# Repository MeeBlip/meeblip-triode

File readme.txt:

---------------------------------------------------------------------------------------------------
                     _     _ _         _        _           _      
                    | |   | (_)       | |      (_)         | |     
 _ __ ___   ___  ___| |__ | |_ _ __   | |_ _ __ _  ___   __| | ___ 
| '_ ` _ \ / _ \/ _ \ '_ \| | | '_ \  | __| '__| |/ _ \ / _` |/ _ \
| | | | | |  __/  __/ |_) | | | |_) | | |_| |  | | (_) | (_| |  __/
|_| |_| |_|\___|\___|_.__/|_|_| .__/   \__|_|  |_|\___/ \__,_|\___|
                              | |                                  
                              |_|                                                                                   
---------------------------------------------------------------------------------------------------

Change log

V1.10 2016.11.12 
- Updated MIDI code to exit interrupt immediately if MIDI command is unrecognized
- Increased front panel switch scanning rate (10X faster)
- Reduced pitchbend to ± 3 semitones
- Altered filter decay envelope to ignore SUSTAIN switch so that filter sweeps continue when key is released
- Removed digital pre-filtering code (previously used on OSC A&B)
- Removed digital enveloping of OSC A & B
- Gate oscillators when amplitude envelope hits zero (prevents audio bleed through)
- Changed filter cutoff curve (use table from MeeBlip SE)
- Scale filter cutoff knob to cover 25%-100% of knob range
- Scale filter resonance knob to cover 25%-100% of knob range
- Added bandlimited square wave tables (pulse waves were previously generated with offset sawtooth ramps)
- Raw calculated waveforms are now used in the lower 4 octaves, then switch to bandlimited wavetables. 
-Flipped waveforms to match phase and avoid a pop when crossing the cut-over point
 
V1.01 2016.10.24 
- Ensure MIDI channel settings are saved correctly when powered off for Channel 1-8 (implement MAXMIDI variable)
- Allow MIDI CC control of GLIDE knob to select waves when in wavetable mode (CC 61 now controls GLIDE in wavetable mode)
- Updated MIDI code to exit interrupt immediately if MIDI command is unrecognized
- Increased front panel switch scanning rate (10X faster)

V1.00 2016.10.19 
- Initial release

---------------------------------------------------------------------------------------------------

  MeeBlip hardware is released under a Creative Commons Attribution-ShareAlike 4.0 International 
	(CC-BY-SA 4.0) license. You are free to share and transform this work, even for commercial
	purposes, providing you:

	1. Give appropriate credit, provide a link to the license, and indicate if changes were made. 
	   You can say something such as "This project is based upon the MeeBlip anode synthesizer. 
	   For more information, visit meeblip.com or download source code and design files at 
	   https://github.com/MeeBlip"

	2. If you remix, transform, or build upon the material, you must distribute your contributions
	   under the same license as the original. That means making source code, design files and PC 
	   board layout files available so someone can build and modify their own version of the project. 

	3. The MeeBlip name is our intellectual property. You are not allowed to release commercial 
	   devices based on our designs using the MeeBlip brand name. 
	
	Here's are links to the Creative Commons license, for the design:
	http://creativecommons.org/licenses/by-sa/4.0/
	http://creativecommons.org/licenses/by-sa/4.0/legalcode

	MeeBlip source code and documentation is released under a GPLv3 license. 

  A copy is available in the MeeBlip repository at:
	https://github.com/MeeBlip/meeblip-anode/blob/master/LICENSE

	MeeBlip Contributors

	Jarek Ziembicki	- Created the original AVRsynth, upon which this project is based.
	Laurie Biddulph	- Worked with Jarek to translate his comments into English, ported to Atmega16
	Daniel Kruszyna	- Extended AVRsynth (several of his ideas are incorporated in MeeBlip)
 	Julian Schmidt	- Original Meeblip digital filter algorithm
	Axel Werner		- Code optimization, bug fixes and new bandlimited waveforms 
	James Grahame 	- Meeblip hardware and firmware development

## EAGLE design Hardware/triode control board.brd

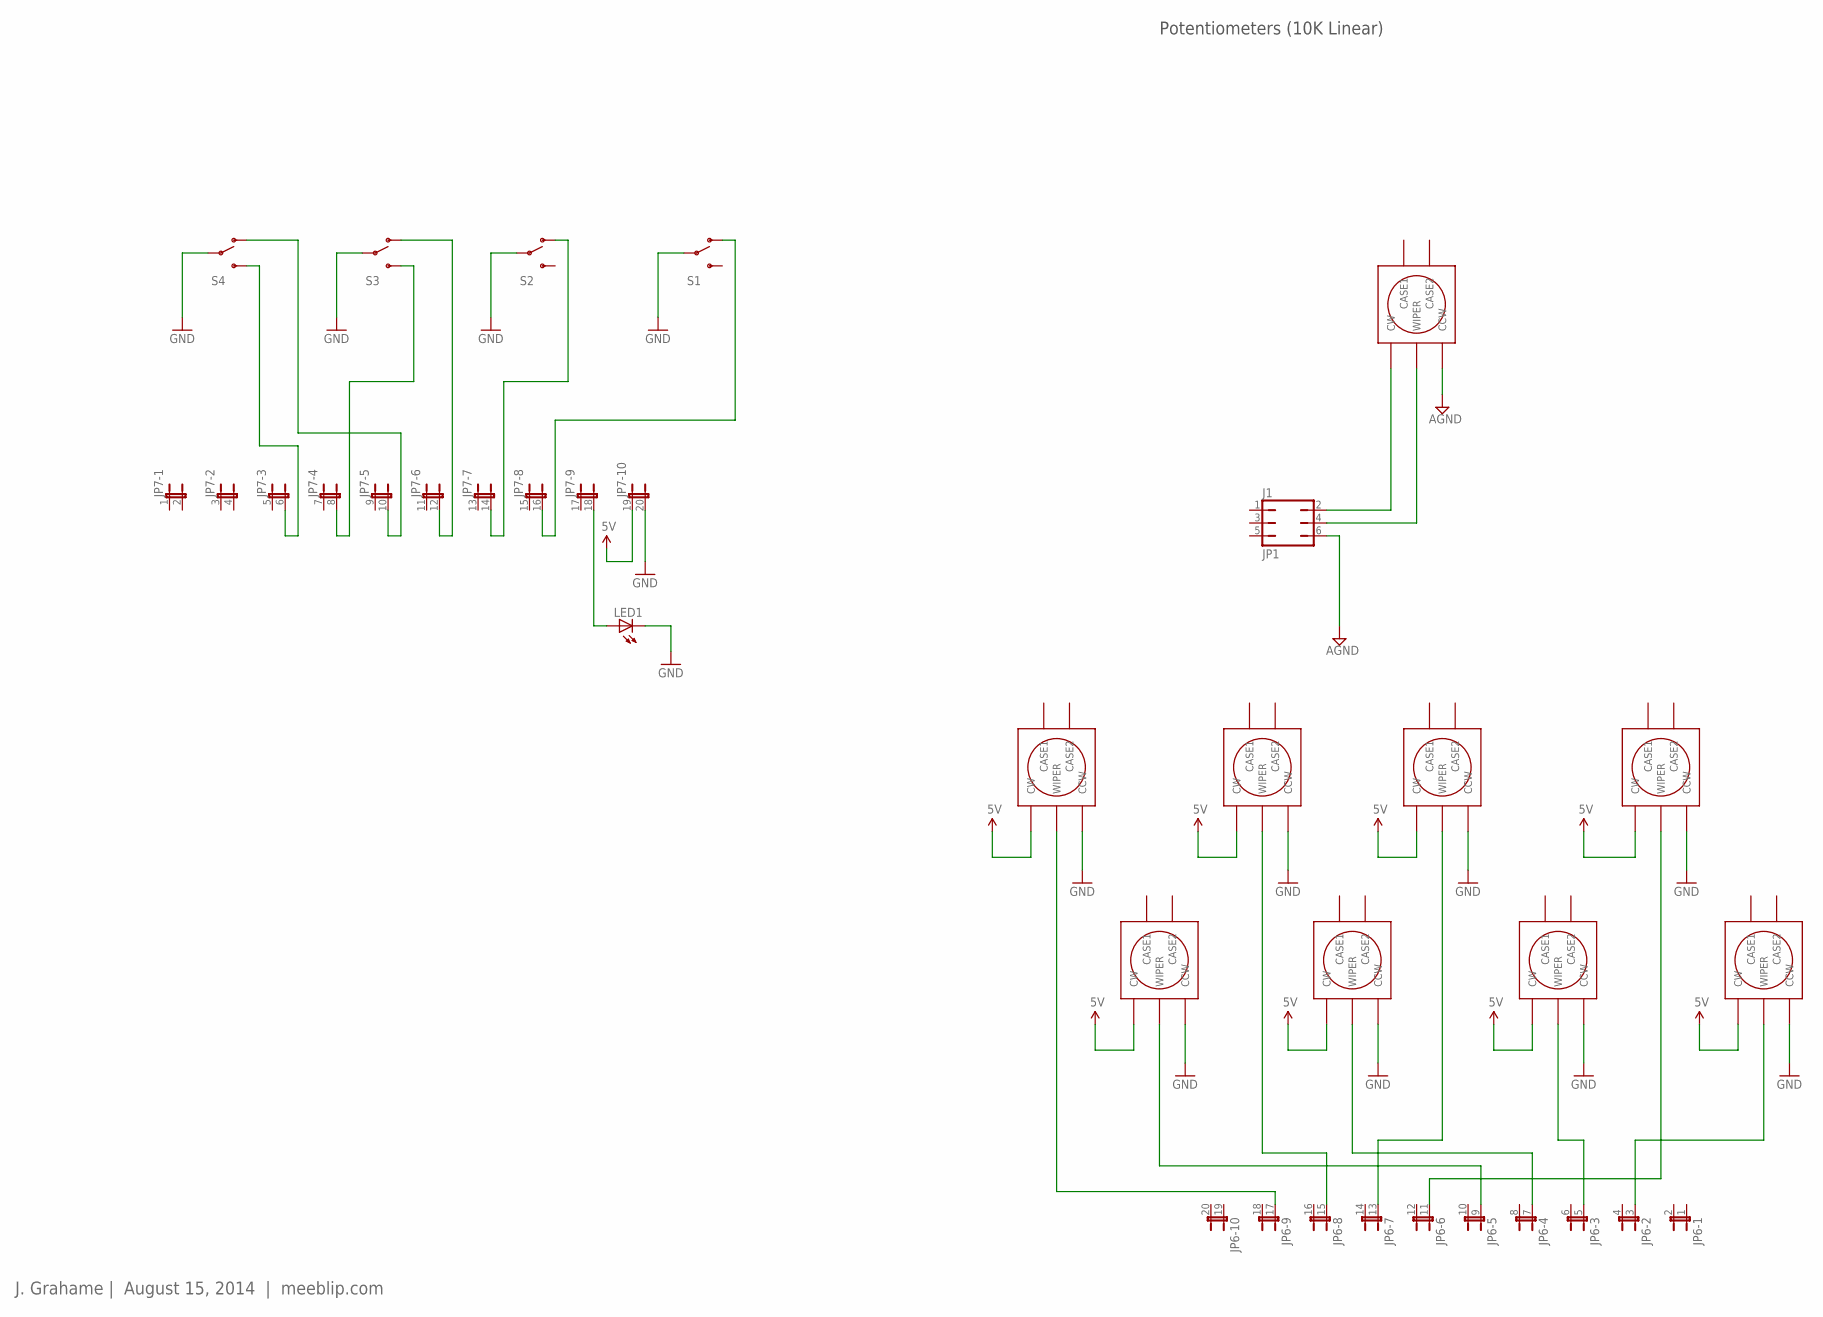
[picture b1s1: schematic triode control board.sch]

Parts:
J1: JP1; JP3Q
JP6, JP7: JP10QE; JP10Q
LED1: LED3MM
POT1, POT2, POT3, POT4, POT5, POT6, POT7, POT8, POT9: VACOLOCO_EVUFRK09_POT; VACOLOCO_EVUF
S1, S2, S3, S4: SWITCH-SPSTMHS122K; SWITCH-SPDT

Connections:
5V: JP7.19 (1), POT2.CW, POT3.CW, POT4.CW, POT5.CW, POT6.CW, POT7.CW, POT8.CW, POT9.CW
AGND: J1.6, POT1.CCW
GND: JP7.20 (2), LED1.K (C), POT2.CCW, POT3.CCW, POT4.CCW, POT5.CCW, POT6.CCW, POT7.CCW, POT8.CCW, POT9.CCW, S1.2, S2.2, S3.2, S4.2
unnamed: J1.2, POT1.CW
unnamed: JP7.18 (2), LED1.A
unnamed: JP6.17 (1), POT2.WIPER
unnamed: JP6.15 (1), POT3.WIPER
unnamed: JP7.16 (2), S1.1 (O)
unnamed: JP7.14 (2), S2.1 (O)
unnamed: JP6.13 (1), POT4.WIPER
unnamed: JP6.9 (1), POT6.WIPER
unnamed: JP6.7 (1), POT7.WIPER
unnamed: JP7.12 (2), S3.1 (O)
unnamed: JP7.10 (2), S4.1 (O)
unnamed: JP6.5 (1), POT8.WIPER
unnamed: JP6.3 (1), POT9.WIPER
unnamed: J1.4, POT1.WIPER
unnamed: JP6.11 (1), POT5.WIPER
unnamed: JP7.6 (2), S4.3 (S)
unnamed: JP7.8 (2), S3.3 (S)

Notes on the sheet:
Potentiometers (10K Linear)
J. Grahame | August 15, 2014 | meeblip.com

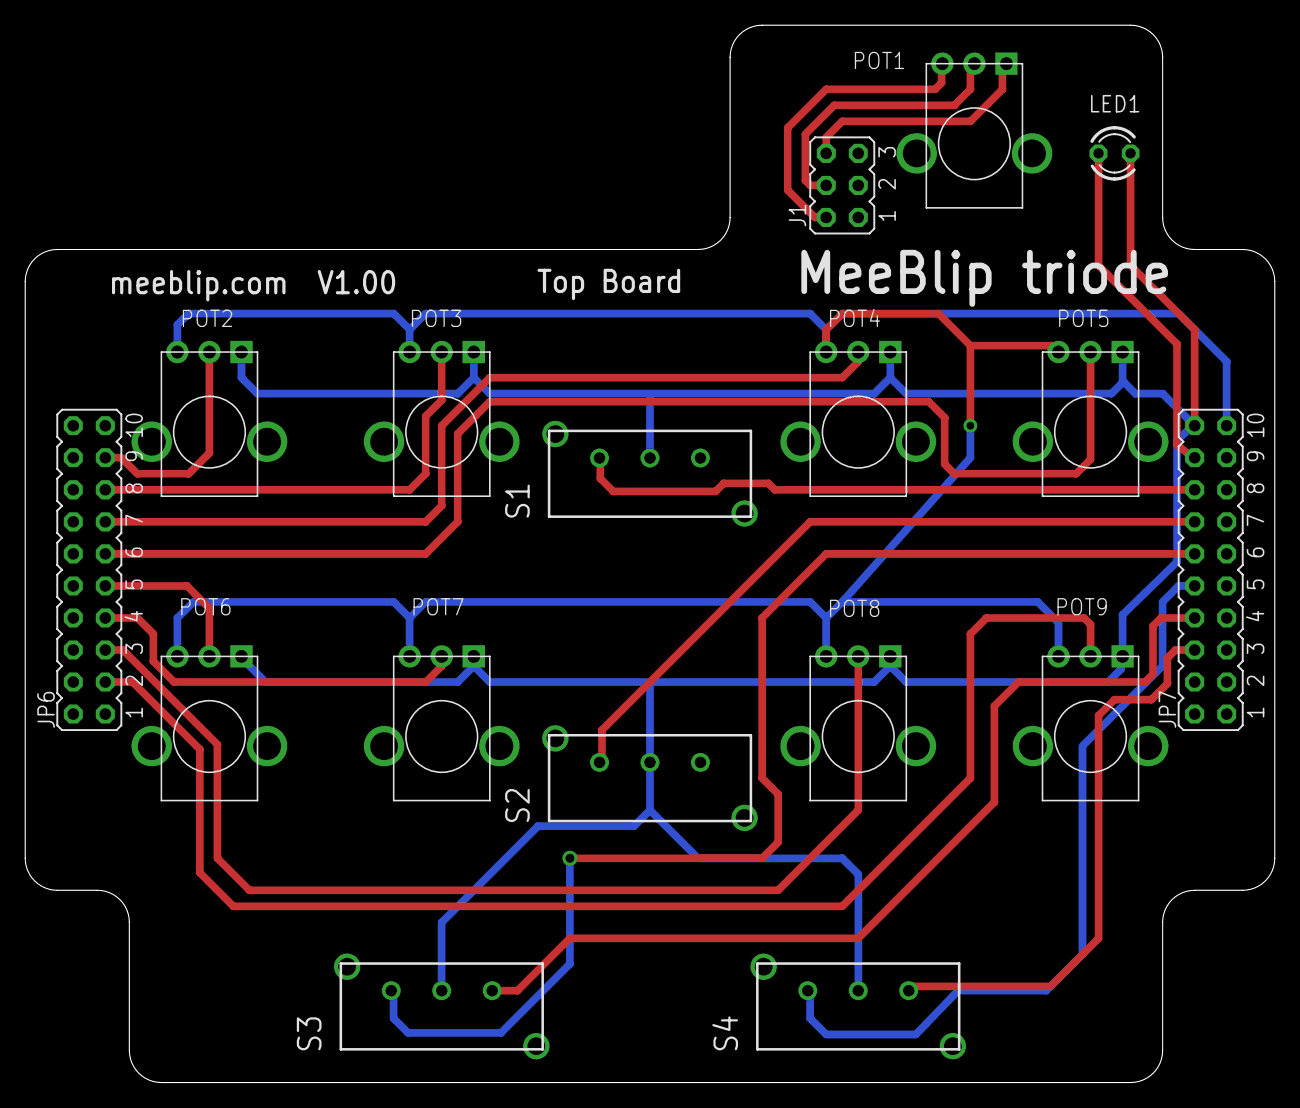
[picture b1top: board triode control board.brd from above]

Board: 2 copper layers, 99.1 x 83.8 mm, 17 parts (0 on the bottom side), 20 nets.

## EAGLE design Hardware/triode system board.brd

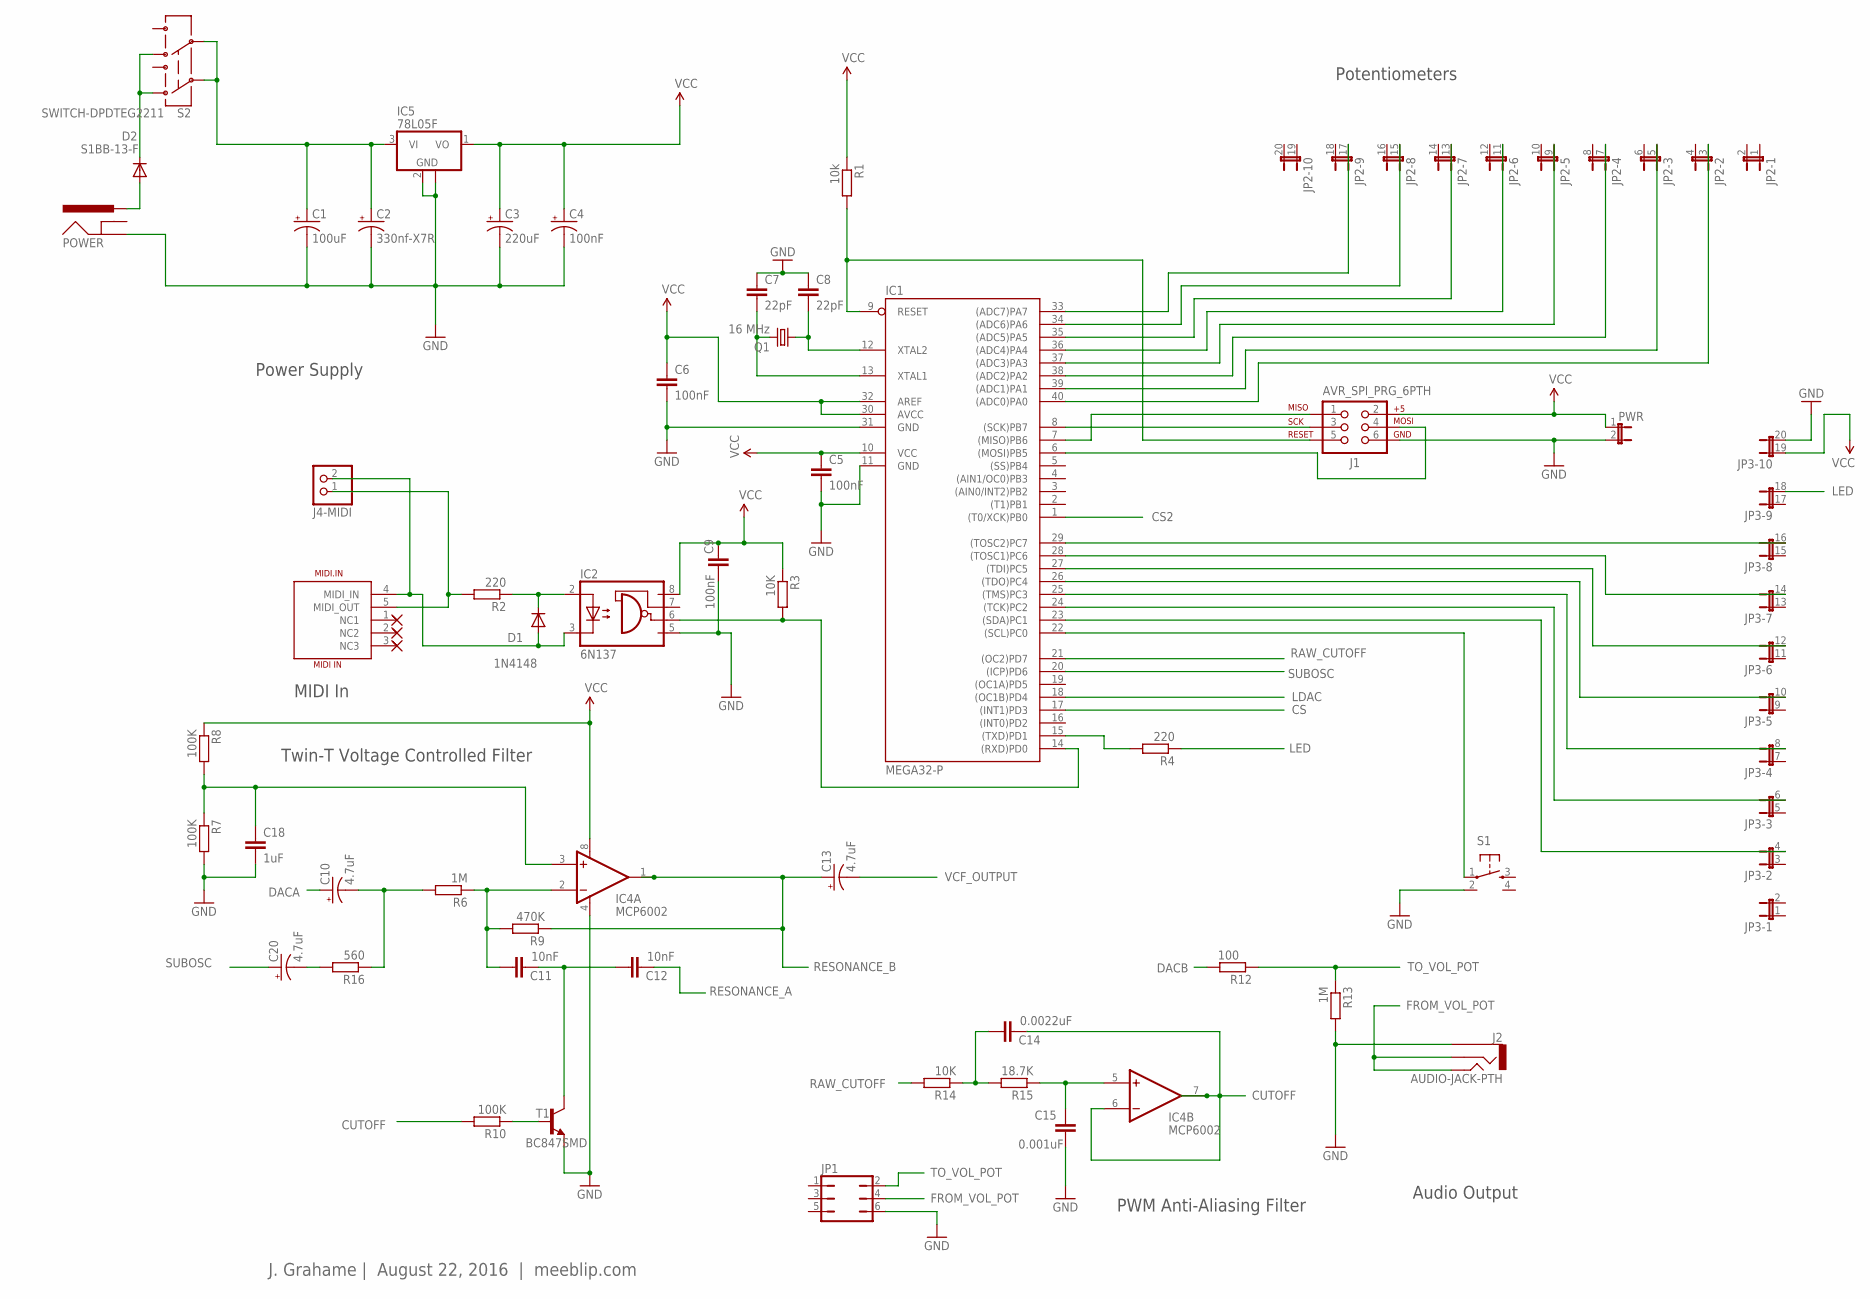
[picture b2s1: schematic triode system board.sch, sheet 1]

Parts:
C1: 100uF; PANASONIC_D
C2: 330nf-X7R; PANASONIC_C
C3: 220uF; PANASONIC_D
C4: 100nF; PANASONIC_C
C5, C6, C9: 100nF; 0603-CAP
C7, C8: 22pF; 0603-CAP
C10, C13, C20: 4.7uF; PANASONIC_C
C11, C12: 10nF; 0603-CAP
C14: 0.0022uF; 0603-CAP
C15: 0.001uF; 0603-CAP
C18: 1uF; 0603-CAP
D1: 1N4148; SOD123
D2: S1BB-13-F; SMA-DO214AC
IC1: MEGA32-P; DIL40
IC2: 6N137; DIL08
IC4: MCP6002; DIL08
IC5: 78L05F; SOT89
J1: AVR_SPI_PRG_6PTH; 2X3
J2: AUDIO-JACK-PTH; AUDIO-JACK
J4-MIDI: PINHD-1X2; 1X02
JP1: JP3Q
JP2, JP3: JP10QE; JP10Q
MIDI.IN: MIDI IN; DIN_5_FEMALE_SUPPORT
POWER: POWER_JACKPTH; POWER_JACK_PTH
PWR: JUMPER-2PTH; 1X02
Q1: 16 MHz; HC49UP
R1: 10k; M1206
R2, R4: 220; M1206
R3, R14: 10K; M1206
R6, R13: 1M; M1206
R7, R8, R10: 100K; M1206
R9: 470K; M1206
R12: 100; M1206
R15: 18.7K; M1206
R16: 560; M1206
S1: TAC_SWITCHPTH; TACTILE-PTH
S2: SWITCH-DPDTEG2211; EG2208A
T1: BC847SMD; SOT23

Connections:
CS: IC1.17 ((INT1)PD3); also elsewhere on the board
CS2: IC1.1 ((T0/XCK)PB0); also elsewhere on the board
CUTOFF: C14.2, IC4.6 (-IN), IC4.7 (OUT), R10.2
DACA: C10.+; also elsewhere on the board
DACB: R12.2; also elsewhere on the board
FROM_VOL_POT: J2.2, J2.5, JP1.4
GND: C1.-, C2.-, C3.-, C4.-, C5.2, C6.2, C7.1, C8.1, C9.2, C15.2, C18.2, IC1.11 (GND), IC1.31 (GND), IC2.5 (GND), IC4.4 (V-), IC5.2 (GND), IC5.2@1 (GND), J1.6, J2.1, JP1.6, JP3.20 (2), POWER.GND, PWR.2, R7.2, R13.2, S1.2, T1.2 (E); also elsewhere on the board
LDAC: IC1.18 ((OC1B)PD4); also elsewhere on the board
LED: JP3.18 (2), R4.1
MIDI-RX: J4-MIDI.1, MIDI.IN.5 (MIDI_OUT), R2.2
MOSI: IC1.6 ((MOSI)PB5), J1.4; also elsewhere on the board
unnamed: C8.2, IC1.12 (XTAL2), Q1.1
unnamed: C7.2, IC1.13 (XTAL1), Q1.2
unnamed: IC1.40 ((ADC0)PA0), JP2.3 (1)
unnamed: D2.K (C), S2.P1-TA (1), S2.P2-TA (4)
unnamed: IC1.7 ((MISO)PB6), J1.1
unnamed: IC1.9 (RESET), J1.5, R1.2
unnamed: IC1.23 ((SDA)PC1), JP3.4 (2)
unnamed: IC1.24 ((TCK)PC2), JP3.6 (2)
unnamed: IC1.25 ((TMS)PC3), JP3.8 (2)
unnamed: IC1.26 ((TDO)PC4), JP3.10 (2)
unnamed: IC1.27 ((TDI)PC5), JP3.12 (2)
unnamed: IC1.28 ((TOSC1)PC6), JP3.14 (2)
unnamed: IC1.15 ((TXD)PD1), R4.2
unnamed: IC1.29 ((TOSC2)PC7), JP3.16 (2)
unnamed: IC1.39 ((ADC1)PA1), JP2.5 (1)
unnamed: IC1.22 ((SCL)PC0), S1.1
unnamed: IC1.38 ((ADC2)PA2), JP2.7 (1)
unnamed: IC1.37 ((ADC3)PA3), JP2.9 (1)
unnamed: IC1.36 ((ADC4)PA4), JP2.11 (1)
unnamed: IC1.35 ((ADC5)PA5), JP2.13 (1)
unnamed: C11.1, IC4.2 (-IN), R6.1, R9.2
unnamed: IC1.34 ((ADC6)PA6), JP2.15 (1)
unnamed: IC1.33 ((ADC7)PA7), JP2.17 (1)
unnamed: IC1.14 ((RXD)PD0), IC2.6 (VO), R3.2
unnamed: D2.A, POWER.PWR
unnamed: C1.+, C2.+, IC5.3 (VI), S2.P1 (2), S2.P2 (5)
unnamed: C20.-, R16.2
unnamed: C18.1, IC4.3 (+IN), R7.1, R8.2
unnamed: C10.-, R6.2, R16.1
unnamed: C11.2, C12.1, T1.3 (C)
unnamed: R10.1, T1.1 (B)
unnamed: D1.C, IC2.2 (A), R2.1
unnamed: D1.A, IC2.3 (C), J4-MIDI.2, MIDI.IN.4 (MIDI_IN)
unnamed: C14.1, R14.1, R15.2
unnamed: C15.1, IC4.5 (+IN), R15.1
RAW_CUTOFF: IC1.21 ((OC2)PD7), R14.2
RESONANCE_A: C12.2; also elsewhere on the board
RESONANCE_B: C13.+, IC4.1 (OUT), R9.1; also elsewhere on the board
SCK: IC1.8 ((SCK)PB7), J1.3; also elsewhere on the board
SUBOSC: C20.+, IC1.20 ((ICP)PD6)
TO_VOL_POT: JP1.2, R12.1, R13.1
VCC: C3.+, C4.+, C5.1, C6.1, C9.1, IC1.10 (VCC), IC1.30 (AVCC), IC1.32 (AREF), IC2.8 (VCC), IC4.8 (V+), IC5.1 (VO), J1.2, JP3.19 (1), PWR.1, R1.1, R3.1, R8.1; also elsewhere on the board
VCF_OUTPUT: C13.-; also elsewhere on the board

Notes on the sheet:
PWM Anti-Aliasing Filter
Audio Output
MIDI In
Power Supply
Potentiometers
J. Grahame | August 22, 2016 | meeblip.com
Twin-T Voltage Controlled Filter

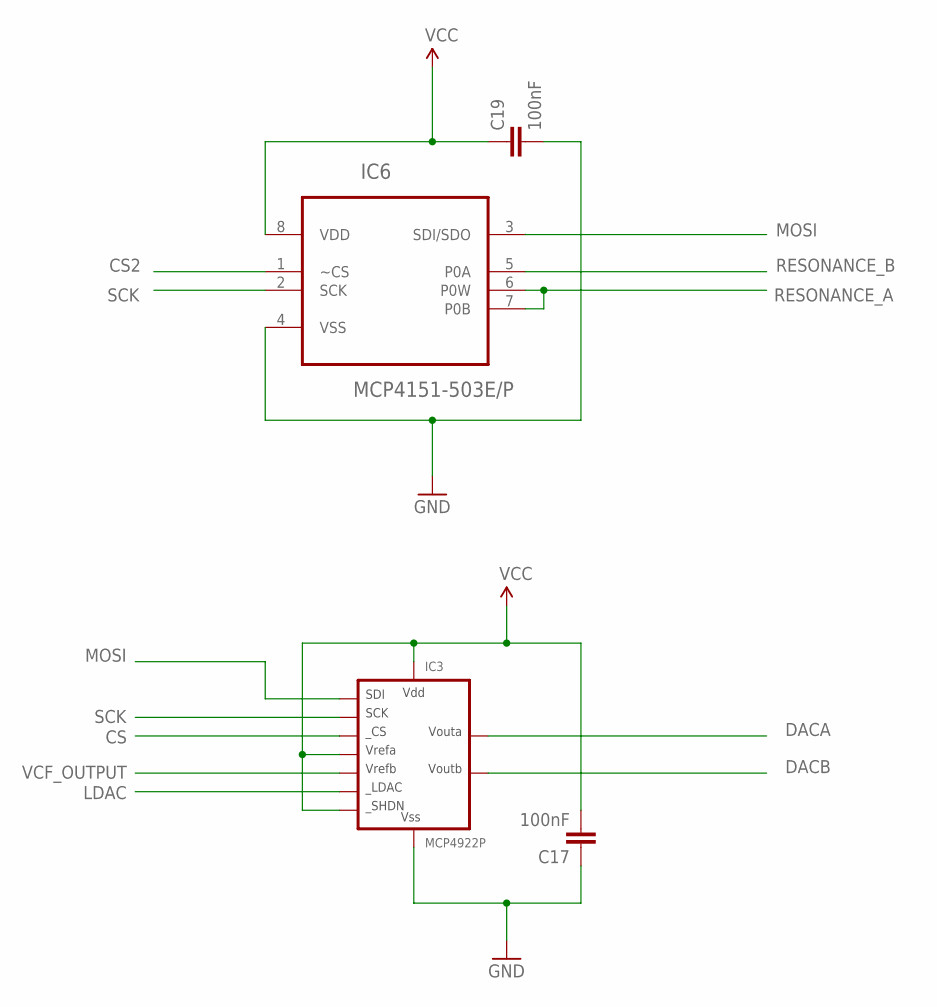
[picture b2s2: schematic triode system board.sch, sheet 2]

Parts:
C17, C19: 100nF; 0603-CAP
IC3: MCP4922P; DIL14
IC6: MCP4151-503E/P; DIP254P762X533-8

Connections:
CS: IC3.3 (CS); also elsewhere on the board
CS2: IC6.1 (~CS); also elsewhere on the board
DACA: IC3.14 (VOUTA); also elsewhere on the board
DACB: IC3.10 (VOUTB); also elsewhere on the board
GND: C17.1, C19.2, IC3.12 (VSS), IC6.4 (VSS); also elsewhere on the board
LDAC: IC3.8 (LDAC); also elsewhere on the board
MOSI: IC3.5 (SDI), IC6.3 (SDI/SDO); also elsewhere on the board
RESONANCE_A: IC6.6 (P0W), IC6.7 (P0B); also elsewhere on the board
RESONANCE_B: IC6.5 (P0A); also elsewhere on the board
SCK: IC3.4 (SCK), IC6.2 (SCK); also elsewhere on the board
VCC: C17.2, C19.1, IC3.1 (VDD), IC3.9 (SHDN), IC3.13 (VREFA), IC6.8 (VDD); also elsewhere on the board
VCF_OUTPUT: IC3.11 (VREFB); also elsewhere on the board

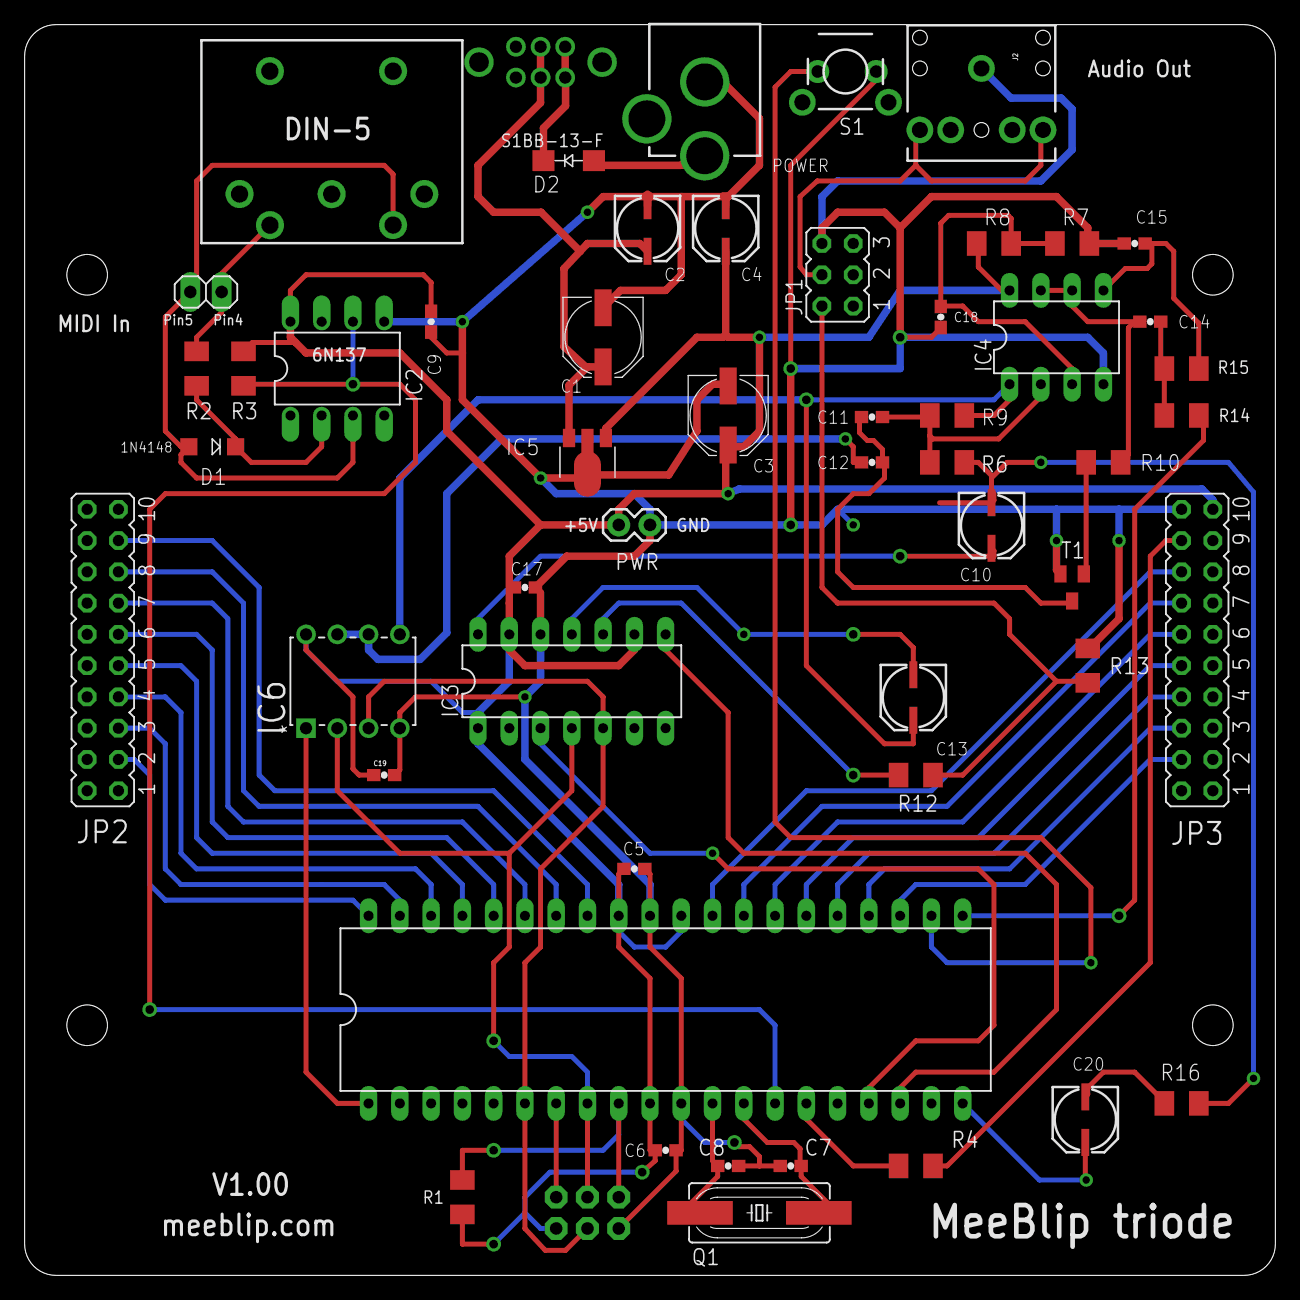
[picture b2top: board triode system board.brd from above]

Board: 2 copper layers, 101.6 x 101.6 mm, 58 parts (1 on the bottom side), 54 nets.

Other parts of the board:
H1, H2, H3, H4: STAND-OFF

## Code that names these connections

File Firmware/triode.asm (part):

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;
;	Port Mapping 
;
;	PA0..7		8 potentiometers
;	PB0			Digipot CS (chip select) for resonance control
;	PB5-PB7		ISP programming header / SPI communication
;	PC0-PC7		Switch inputs
;	PD0		    RxD (MIDI IN)
;	PD1		    Power ON/MIDI LED
;	PD3		    DAC CS (chip select)
;	PD4			LDAC (DAC load signal)
;	PD6			Sub-Oscillator output
;	PD7			RAW Filter Cutoff control voltage (PWM generated)
;	
;
;	Timers	
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
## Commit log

2016-10-19 :boom::camel: Added .gitattributes & .gitignore files
2016-10-19 MeeBlip triode
    MeeBlip triode monophonic MIDI synthesizer
2016-10-26 triode V1.01
    Minor bug fixes and additions
2016-11-13 Version 1.10
    Bug fixes, improvements
2016-11-13 Version 1.10
2016-11-23 Version 1.11
    Minor update
2016-11-23 Version 1.11
2017-03-08 MIDI update
    Patched MIDI interrupt to work with MIDI Clock.
